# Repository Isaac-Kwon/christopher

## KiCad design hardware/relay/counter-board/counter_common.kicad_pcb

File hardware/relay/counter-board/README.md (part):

# 릴레이 계수기 보드 (Phase 3 R 트랙, 회로도)

작성일: 2026-11-15 · 상태: **회로도(KiCad 10) 생성·ERC·넷리스트 시뮬레이션 완료, 기판 배치(미배선) 생성·검증 완료, 결정 0003 8.4절(K1–K7) 반영(10절, K7 = 클럭 버스 B와 레일 버퍼는 11절), 배선은 사용자가** · 관련: `hardware/relay/concept.md` 5·6절, `docs/decisions/0001-test-register-timing.md`, `docs/decisions/0003-interfaces.md`, `hardware/relay/sequencer/README.md`(클럭 순서기, `CLK_A`/`CLK_B`), `hardware/common/design-brief.md`, `hardware/relay/shifter-board/README.md`, 기준 모델 `crates/christopher-core/src/relay.rs`(`Counters`, `Controls::from_cores`)

**표기.** **(계산)** = 이 문서의 산술, **(추정)** = 실측 전 값, **(미확인)** = 데이터시트로 확인하지 못한 것.

## 1. 무엇인가

`concept.md` 5.1절의 계수기 다섯 개(pL, pM, a3, a2, a1)와 a4 = l, 그리고 결정 0003이 더한 뱅크 수준의 r 자리(pR)를 릴레이와 다이오드(+ 저항, LED)만으로 만든다. 출력은 시프터 보드 J5의 `CTRL0..CTRL4`(24 V, 가중치 1, 2, 4, 8, 16)를 **그대로** 구동하는 5비트 이진값 0..25다. 모든 자리는 같은 회로(**릴레이 11개**)이고 보드는 두 장이다.

| 보드 | 내용 | 릴레이 | 다이오드 | 파일 |
|---|---|---:|---:|---|
| 공통 (`counter_common`) | pL(= a4 = l), pM, a3 = l − m, **pR(r, 프리셋 0)** 네 자리 + 자리 사이 규칙 배선 + **`POS` 커넥터 J4** + 전원 입력 J3 + **클럭 버스 B의 레일 버퍼**(pL·pM 주 릴레이의 쌍둥이 10개, `CLOCK_B` J5, `UNIT_BUS_B` J6; 11절) | 54 (44 + 10) | 279 | `counter_common.kicad_sch`, `common_pl/pm/a3/pr.kicad_sch` |
| 유닛별 (`counter_unit`) | a2, a1 두 자리(오프셋 다이얼 프리셋) + 공통 a3/a4 코드를 이 유닛의 시프터 보드 4장으로 중계하는 릴레이 10개 + 전원 입력 J7 | 32 (22 + 10) | 138 | `counter_unit.kicad_sch`, `unit_a2/a1/buf.kicad_sch` |

생성기 `gen_counter.py`(표준 라이브러리만, 시프터 보드와 같은 방식·심볼: `Relay:G6S-2`, D-sub, 라벨 연결), 검증기 `verify_counter.py`. 생성물은 UUID를 고정해 두었으므로 손으로 고치지 말고 생성기를 고친다.

## 2. 한 자리의 회로 (11 릴레이)

### 2.1 아이디어

비트마다 **슬레이브 릴레이 KS**(값을 갖고, 접점이 `CTRL`을 구동)와 **마스터 릴레이 KM**(항상 KS의 **반대값**을 따라가는 거울)을 둔다. 한 자리의 증가는 이진 올림 사슬에서 "토글해야 하는 비트"를 가려내고, 그 비트의 슬레이브가 마스터 값을 **한꺼번에** 받는 동작이다: 토글이므로 새 값 = 마스터 값 = 옛 값의 반대. 마스터가 클럭 동안 변하지 않으므로 올림 사슬은 접점만 지나가고 릴레이 동작을 기다리지 않는다(파문 올림이 아니라 순간 전달, 경주 없음).

신호는 모두 24 V "레일"(접점·다이오드를 거쳐 전달되는 +24 V)이고, 증가/정지는 상보 쌍으로 다룬다.

| 이름 | 뜻 |
|---|---|
| `AIN` / `ZIN` | 증가 레일 / 정지 레일 (항상 하나만 켜짐, 클럭 구간에서 `AIN` = 클럭 펄스 ∧ 이 자리의 증가 조건) |
| `AOUT` / `ZOUT` | 올림(25 → 0) 레일 쌍 = 다음 자리의 `AIN` / `ZIN` 재료 |
| `NOUT` | `AIN` ∧ (값 ≠ 25) |
| `P0..P4` | 프리셋 코드(다이얼). 24 V는 `LOAD` 동안에만 걸린다 |
| `Q0..Q4` | 값의 각 비트(1이면 24 V) = `CTRL` |

### 2.2 구성 (비트 i = 0..4)

- **KS_i** (극 1: COM = +24 V, NO → `Q_i`, NC → `NQ_i`; 극 2: COM = 레일 `Z_i`, NC → 마스터 거울, NO → 자기 유지).
- **KM_i** (극 1: COM = 사슬 `A_i`, NC → `A_{i+1}`(사슬 계속), NO → `G_i`(마스터 유지 + 슬레이브 적재 급전); 극 2: COM = `AIN`, NO → `Y_i` = `AIN` ∧ KM_i).
- **KW** (한 자리에 하나): 코일 = `NQ0 ∨ NQ4 ∨ NQ3`(다이오드 OR) = "값 ≠ 25". 접점 두 극이 비트 1, 2의 마스터 거울 경로에 직렬로 들어간다.
- 올림 사슬: `A_0 = AIN`, `A_{i+1} = A_i ∧ (마스터 i = 0)`(마스터 NC 접점) → 비트 i는 `A_i`가 올라올 때 토글. `A_5` = `AOUT`.
- 정지 레일: `Z_t = ZIN ∨ Y_0 ∨ … ∨ Y_{t−1}`(병렬 다이오드 OR, 한 노드에 다이오드 한 개 전압 강하) = `NOT A_t`.
- 슬레이브 코일 급전(다이오드로 OR): ① 자기 유지(레일 `Z_i` → KS 극 2 NO), ② 적재(`A_i` → KM NO = `G_i`, 마스터가 1일 때), ③ 프리셋(`P_i`). 마스터 코일 급전: ① 거울(레일 `Z_i` → KS 극 2 NC; 비트 1, 2는 KW 접점 경유), ② 유지(`G_i`).
- 코일마다 역기전력 다이오드(1N4148W), 급전·OR 다이오드는 쇼트키(1N5819W, 강하 약 0.3 V — 코일 전압 확보). 비트마다 `Q`에 저항 4.7 kΩ + LED(값 표시, 5 mA).

### 2.3 동작 (한 클럭)

클럭은 **두 상**이다. `NCK`(= 평상시 켜짐)와 `CK`(= 확정 펄스). 상보이며 겹치지 않는다(2.5절).

| 상 | 레일 | 마스터 | 슬레이브 |
|---|---|---|---|
| φ1 (`NCK`, 평상시) | 모든 `Z_i`가 켜짐, `A_i` 꺼짐 | 슬레이브의 반대값을 계속 따라감(**미리 계산**) | 자기 유지 |
| φ2 (`CK`, 확정) | `AIN`이 켜진 자리: 토글 비트의 `Z_i`가 꺼지고 `A_i`가 켜짐 | 토글 비트: 자기 유지(`G`)로 값을 붙잡음. 나머지: 계속 거울 | 토글 비트: 마스터 값을 받음. 나머지: 유지 |

- **정지**: `AIN` = 0이면 모든 `A_i` 꺼짐, 모든 슬레이브가 `Z_i`로 유지된다.
- **25 → 0**: 값이 25 = `11001b`일 때 KW가 꺼져 비트 1, 2의 거울이 끊기고(마스터는 `00000`), 이때만 마스터 전부가 0이 된다(정상 값에서 마스터 = NOT 값이 0이 되려면 값 = 31이어야 하므로 도달 불가). 마스터 NC가 모두 닫혀 있으므로 `A_0 … A_4`가 전부 올라와 슬레이브 다섯 개가 모두 0을 받는다. `A_5`가 올라와 **올림 = `AOUT` = `AIN` ∧ 값 = 25**가 된다. 따라서 25 → 0을 별도 감지·리셋 없이(과도 값 26 없이) 같은 사슬이 처리한다.
- 정상 증가에서 `A_{i+1} = A_i ∧ 슬레이브 i`이므로 이진 +1과 같다. 이진 코드 직접 구동이므로 시프터에 중간값이 안 보인다.
- `ZOUT = NOT AOUT`는 정지 레일이 상보를 유지하게 하는 쌍이다(`NCK`가 꺼진 φ2에서도 올림이 없으면 켜짐).

### 2.4 릴레이 수 (concept.md 추정과 비교)

한 자리: KS 5 + KM 5 + KW 1 = **11개**. `concept.md` 5.2절의 "비트당 2개 × 5 + 리셋·올림 2–3개 ≈ 13개"보다 2개 적다(올림은 마스터 접점 사슬이 하고, 26진 처리는 KW 하나다). 대신 다이오드가 한 자리 64개다(급전 25 + 정지 레일 OR 20 + `NOUT` OR 5 + KW 3 + 역기전력 11). 2연 다이오드 소자(SOT-23)를 쓰면 부품 수는 절반 근처로 준다 **(추정)**.

| 보드 | 자리 | 릴레이 | 비고 |
|---|---|---:|---|
| 공통 | pL, pM, a3 | 33 | `concept.md` 5.2절의 공통 계수 39 대비 −6 (클럭 발생·시작·정지·Home 제어 약 8은 별도 시퀀서) |
| 유닛 | a2, a1 | 22 | `concept.md`의 26 대비 −4 |
| 유닛 | a3/a4 중계 | 10 | 코일 = 공통 코드선, 접점 두 극 병렬 = 이 유닛의 `CTRL` 선 (`concept.md`의 "중계 릴레이 약 10") |
| 유닛 합계 | | **32** | `concept.md` 36 대비 −4 |
| 6유닛 합계 | | **225** (= 33 + 6 × 32) | `concept.md` 266 대비 |
| 12유닛 합계 | | **417** | `concept.md` 482 대비 |

이 비교에는 그 뒤에 더한 공통 보드의 pR(11개, 0003 K3)과 클럭 버스 B의 쌍둥이 주 릴레이(10개, 0003 K7, 11절)가 들어 있지 않다. 지금의 공통 보드는 54개, 12유닛 합계는 438개(= 54 + 12 × 32)다 **(계산)**.

(공통 클럭 발생·시퀀서는 이 보드에 없다.)

### 2.5 시퀀서에 요구하는 것

- `CK`/`NCK`는 **하나의 전환(c) 접점**에서 나온다(COM = +24 V, NO → `CK`, NC → `NCK`). 개별 릴레이 둘로 만들어 둘 다 켜지면 값이 틀어진다(시뮬레이션에서 확인: "info" 줄). 전환 중 양쪽이 모두 꺼지는 순간(break-before-make)은 릴레이 복귀 시간(3–5 ms, 결정 0001)보다 충분히 짧아야 한다(수 백 µs).
- **HOME(프리셋)**: ① `CK` = `NCK` = 0(전부 꺼짐)으로 모든 릴레이를 풀고, ② `LOAD` = 24 V로 다이얼 공통선에 전압을 걸어 슬레이브가 `P`를 받게 하고, ③ `NCK`를 올리되 **`LOAD`는 그 뒤에 내린다**(겹침 또는 틈 없이). `LOAD`가 `NCK`보다 먼저 내려가는 틈이 릴레이 복귀 시간보다 길면 프리셋이 지워진다(시뮬레이션: 틈 있는 순서는 실패).
- 전원 투입 직후의 릴레이 상태는 임의이며, 위 절차가 어떤 상태에서도 올바른 값을 만든다(무작위 초기 상태로 확인).

## 3. 계수 규칙의 배치 (`relay.rs` `Counters`)

| 계수기 | 증가 조건 | 구현 (`AIN` / `ZIN`) |
|---|---|---|
| pL (a4 = l) | 매 클럭 | `AIN = CK`, `ZIN = NCK` |
| pM | l이 25 → 0 | `AIN = LC` (= pL의 `AOUT`), `ZIN = ZL` (= pL의 `ZOUT`) |
| a3 = l − m | 매 클럭, 단 l이 25 → 0이면 정지 | `AIN = NL` (= pL의 `NOUT` = `CK ∧ l ≠ 25`), `ZIN = NCK ∨ LC` (다이오드 2개) |
| a2 | pM이 증가하고 m이 25 → 0이 아님 | `AIN = A2B` (= pM의 `NOUT` = `CK ∧ l 올림 ∧ m ≠ 25`, pM의 접점 극 2의 COM을 `LC`로 둔 덕분에 다이오드 없이 AND), `ZIN = Z2B = ZL ∨ A1B` (다이오드 2개) |
| a1 | m이 25 → 0 | `AIN = A1B` (= pM의 `AOUT`), `ZIN = Z1B` (= pM의 `ZOUT`) |

- **공통 보드**: 위 다섯 규칙 전부와 pM·a3 자리의 판정이 여기 있다. 유닛으로는 레일 4개(`A2B`, `Z2B`, `A1B`, `Z1B`)와 a4/a3 코드 10선(`L0..4`, `T0..4`)만 나간다.
- **유닛 보드**: 규칙 논리가 **없다**. a2/a1 자리는 공통 레일을 받아 증가/정지만 하고, 프리셋만 유닛별이다(다이얼: a1 = k, a2 = −k mod 26).
- pL·pM·a3의 `P0..P4`는 0 V에 묶어 **프리셋 = 0(clear)**. 오프셋과 무관하게 HOME에서 l = m = 0, a3 = 0이다.
- 모든 올림·판정이 **마스터 값**(φ2 동안 불변)에서 나오므로, 같은 클럭에서 슬레이브가 바뀌어도 규칙 신호가 흔들리지 않는다. 한 클럭의 모든 계수기가 같은 `CK` 펄스 안에서 동시에 움직이고, 사이의 순서(예: pM이 l보다 먼저/나중)가 없다.

## 4. 타이밍 (결정 0001과의 관계)

위치 한 칸(`concept.md` 6절)의 순서: **`CK` 펄스 → 슬레이브 전환 → (a3/a4는 중계 릴레이) → 시프터 전환·바운스 → `STROBE` → 감지 → `JUDGE` → `CLEAR` → `CK` 복귀 → 다음 `CK`**.

| 구간 | 대표 | 최대 | 비고 |
|---|---:|---:|---|
| 슬레이브 동작 (`CK` 상승부터) | 2.5 | 4 | a1, a2는 여기서 `CTRL` 확정 |
| a3/a4 중계 릴레이 | 2.5 | 4 | a3, a4만 해당(슬레이브 + 중계 = 5 / 8 ms). a1, a2는 중계 없이 슬레이브 접점이 시프터 코일을 구동 |
| `CK` 펄스 폭 | | ≥ 4 + 튐 1 = 5 | 슬레이브가 끝까지 움직일 때까지 `CK` 유지 **(계산)** |
| 마스터 재계산 (`CK` 하강부터) | 2.5 | 4 (복귀는 다이오드 포함 최대 10) | 슬레이브가 바뀐 뒤 KW와 마스터가 새 거울을 만든다. **`STROBE`·판정과 겹치는 구간**이므로 위치 시간에 더해지지 않는다 |

- 결정 0001의 표(대표 약 20 ms, 최대 약 33 ms)에서 계수기 항목(릴레이 2단, 대표 5 / 최대 8 ms)과 중계 릴레이(2.5 / 4 ms)는 이 설계에서 a3/a4 경로 = 슬레이브 + 중계(5 / 8 ms)와 a1/a2 경로 = 슬레이브 1단(2.5 / 4 ms)으로 줄어든다. 마스터는 "미리 계산"으로 클럭 경로 밖에 있으므로 클럭 경로에는 **슬레이브 1단**만 있다. 그러므로 표의 두 항목 합(7.5 / 12 ms)이 최악 경로 5 / 8 ms로 줄어 합계는 대표 약 17.5 / 최대 약 29 ms **(계산)**.
- 마스터가 다음 `CK` 전에 정착해야 한다: 슬레이브(4) → KW(4) → 마스터(복귀 최대 10) ≈ 18 ms 최대 **(계산)**. `CK` 하강부터 다음 상승까지 25 ms 목표에서 `CK` 폭 5 ms를 빼면 20 ms가 남아 맞는다. 33 ms 예비안에서도 성립. 이 여유는 R.1에서 실측(항목 2).
- `JUDGE`·`CLEAR`는 테스트 레지스터 쪽 신호이며 계수기와 신호를 주고받지 않는다. 다음 `CK`는 `CLEAR` 뒤에만 나가도록 클럭 시퀀서가 정한다(계수기 보드는 이를 모른다).
- 관찰 모드(≤ 4 위치/초)와 한 스텝 버튼: `CK`를 한 번 누르는 것이 한 클럭이다. 마스터가 자동으로 다음 값을 준비해 두므로 버튼 사이 간격에 제약이 없다.

## 5. 커넥터

모두 D-sub 수(핀) 직각 PCB 장착, 케이블은 암–암(시프터 보드 규약과 같음).

| 보드 | 참조 | 이름 | 핀 |
|---|---|---|---|
| 공통 | J1 | CLOCK (DE9) | **클럭 버스 A**(순서기 J3 `CLK_A`): 1 `CK`, 2 `NCK`, 3 `LOAD`, **4–5 예약(전에는 +24 V)**, 6–7 0 V, 8–9 예약 |
| 공통 | J2 | UNIT_BUS (DB25) | **유닛 1–6**: 1 `A2B`, 2 `Z2B`, 3 `A1B`, 4 `Z1B`, 5–9 `L0..L4`(a4 = l 코드), 10–14 `T0..T4`(a3 코드), 15 `LOAD`, **16–18 예약(전에는 +24 V)**, 19–21 0 V, 22–25 예약 |
| 공통 | J5 | CLOCK_B (DE9) | **클럭 버스 B**(순서기 J4 `CLK_B`), J1과 같은 배치: 1 `CK_B`, 2 `NCK_B`, 3 `LOAD_B`, 4–5·8–9 예약, 6–7 0 V. 11절 |
| 공통 | J6 | UNIT_BUS_B (DB25) | **유닛 7–12**, J2와 같은 배치: 1 `A2B_B`, 2 `Z2B_B`, 3 `A1B_B`, 4 `Z1B_B`(버스 B의 레일, J5에서만 먹음), 5–14 `L0..L4`·`T0..T4`(J2와 같은 넷), 15 `LOAD_B`, 16–18·22–25 예약, 19–21 0 V. 유닛 보드는 같은 것이고 어느 리본에 꽂히는지만 다르다. 11절 |
| 공통 | J3 | 24V_IN (5.08 mm 2극 단자) | 1 = +24 V, 2 = 0 V. 보드의 +24 V는 여기서만 받는다(PTC 1 A → 직렬 P채널 MOSFET → TVS 33 V + 100 µF) |
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
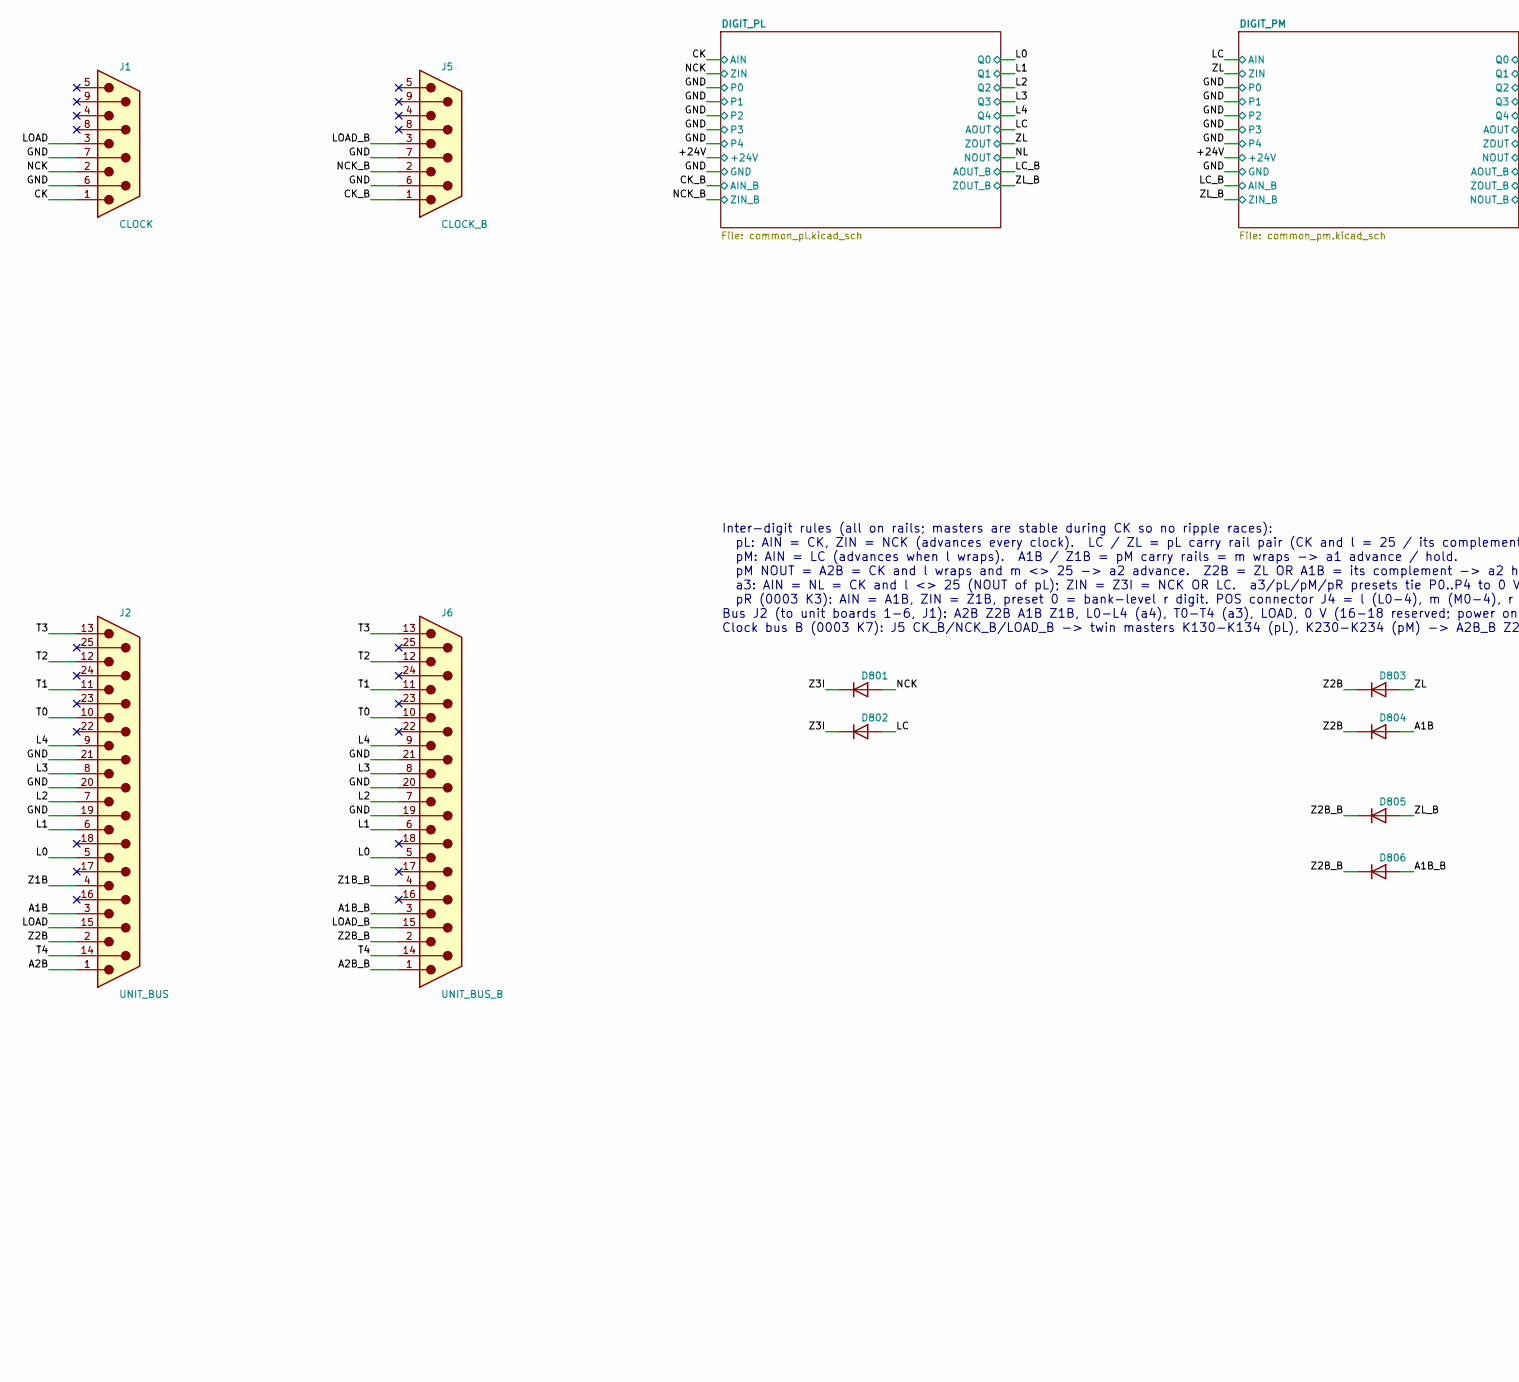
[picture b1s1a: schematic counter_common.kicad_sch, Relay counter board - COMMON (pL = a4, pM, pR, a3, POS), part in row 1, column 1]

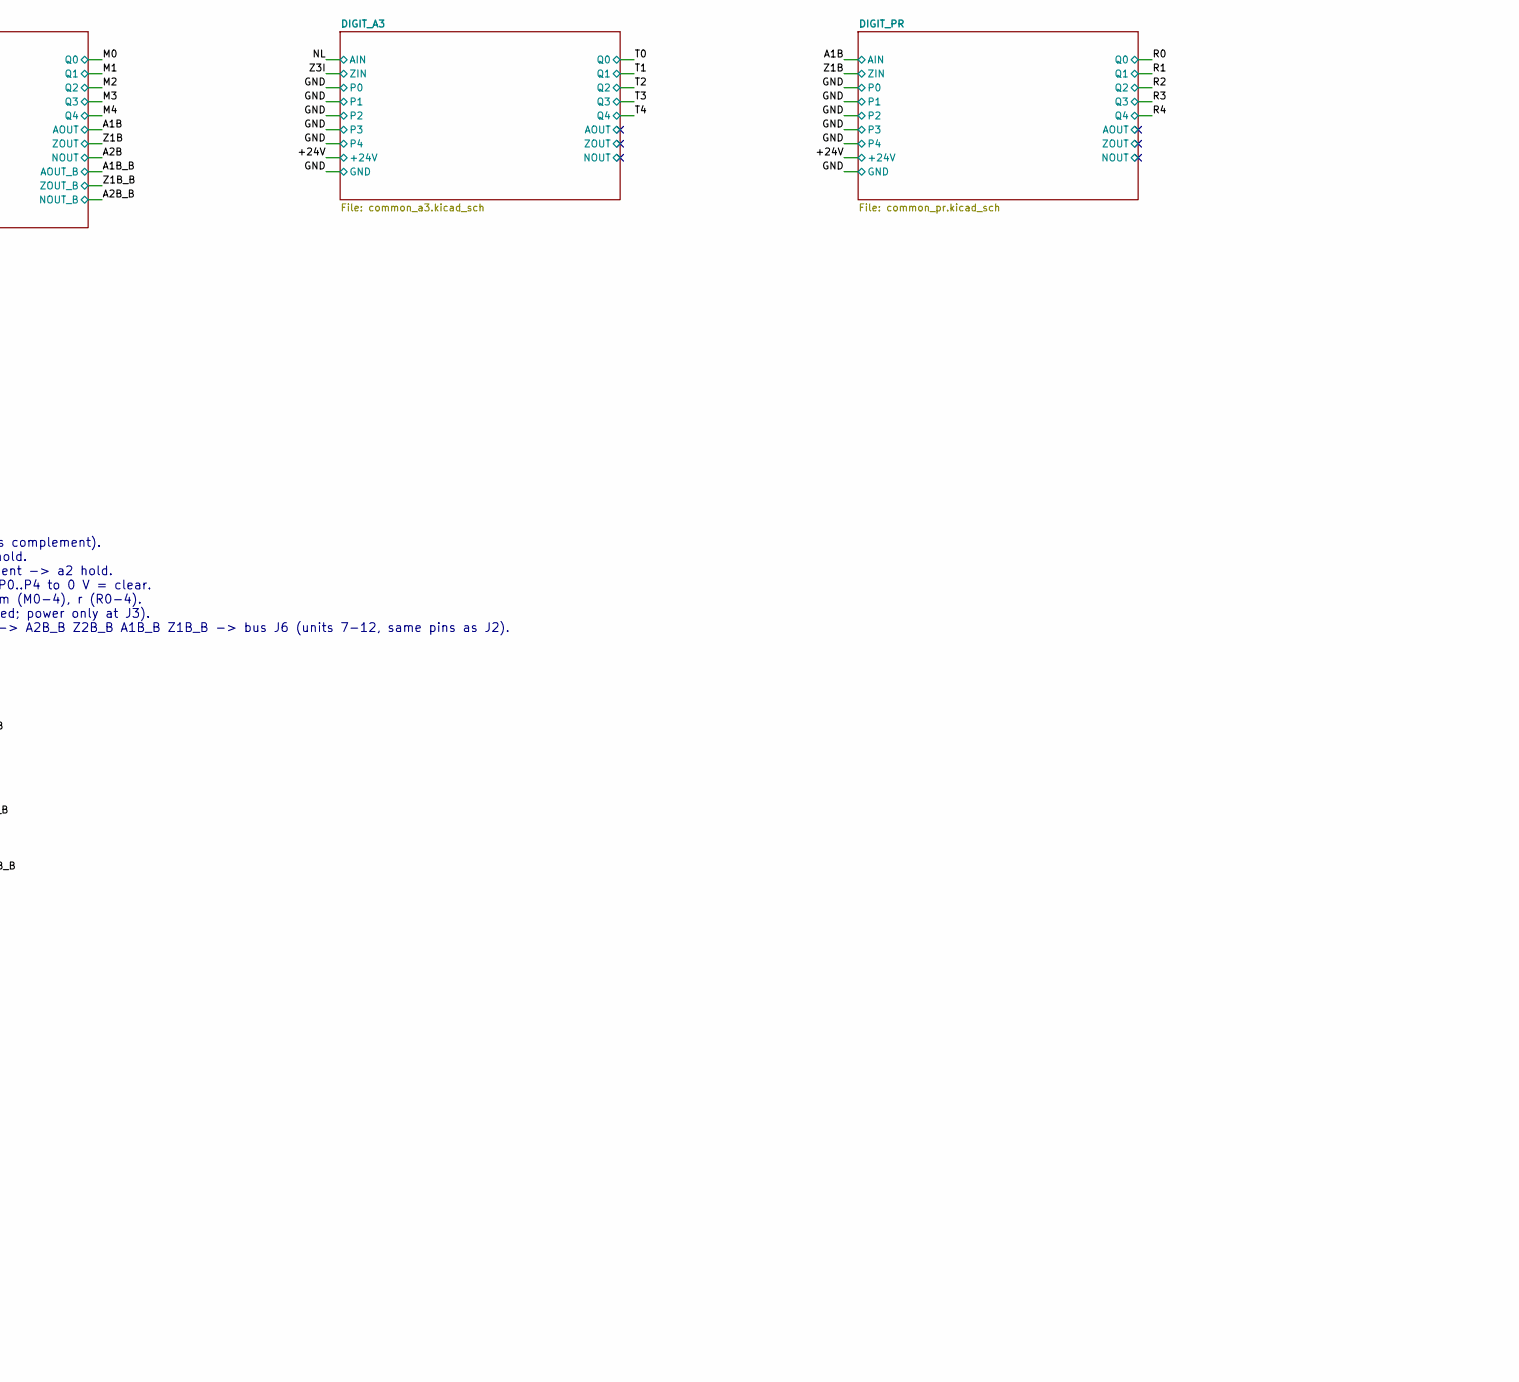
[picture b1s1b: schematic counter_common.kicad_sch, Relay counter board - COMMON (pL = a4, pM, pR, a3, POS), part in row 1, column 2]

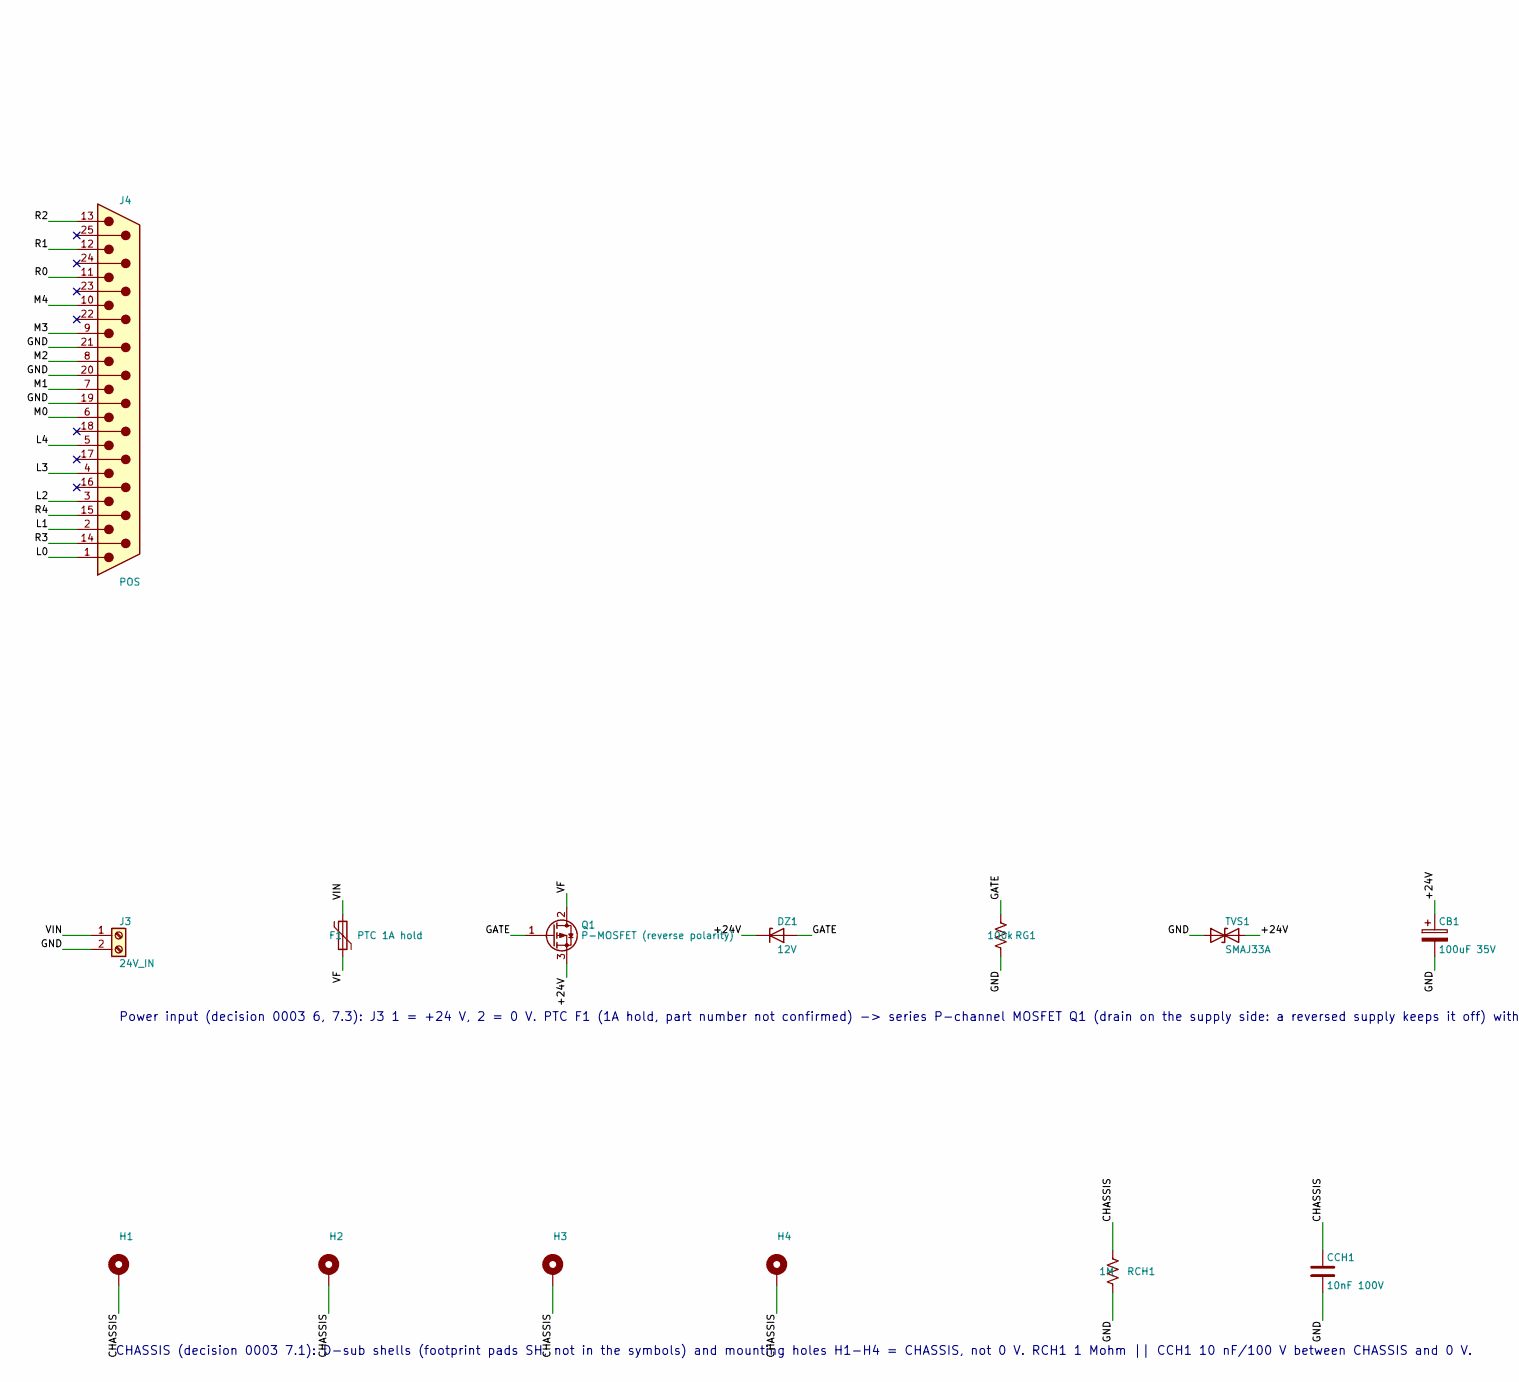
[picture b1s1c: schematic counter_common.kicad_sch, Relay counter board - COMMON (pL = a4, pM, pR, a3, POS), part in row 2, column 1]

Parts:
CB1: 100uF 35V; CP_Radial_D8.0mm_P3.50mm
CCH1: 10nF 100V; C_0603_1608Metric
D801, D802, D803, D804, D805, D806: 1N5819W; D_SOD-123
DZ1: 12V; D_SOD-123
F1: PTC 1A hold; Fuse_1812_4532Metric
H1, H2, H3, H4: MountingHole_Pad; MountingHole_3.2mm_M3_Pad
J1: CLOCK; DSUB-9_Pins_Horizontal_P2.77x2.84mm_EdgePinOffset9.90mm_Hou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
J2: UNIT_BUS; DSUB-25_Pins_Horizontal_P2.77x2.84mm_EdgePinOffset9.90mm_Ho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
J3: 24V_IN; TerminalBlock_Phoenix_MKDS-1,5-2-5.08_1x02_P5.08mm_Horizont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
J4: POS; DSUB-25_Pins_Horizontal_P2.77x2.84mm_EdgePinOffset9.90mm_Ho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
J5: CLOCK_B; DSUB-9_Pins_Horizontal_P2.77x2.84mm_EdgePinOffset9.90mm_Hou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
J6: UNIT_BUS_B; DSUB-25_Pins_Horizontal_P2.77x2.84mm_EdgePinOffset9.90mm_Ho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
Q1: P-MOSFET (reverse polarity); SOT-223-3_TabPin2
RCH1: 1M; R_0603_1608Metric
RG1: 100k; R_0603_1608Metric
TVS1: SMAJ33A; D_SMA

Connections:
/+24V: CB1.1, DZ1.1 (K), Q1.3 (S), TVS1.2 (A2); also elsewhere on the board
/A1B: D804.2 (A), J2.3; also elsewhere on the board
/A1B_B: D806.2 (A), J6.3; also elsewhere on the board
/A2B: J2.1; also elsewhere on the board
/A2B_B: J6.1; also elsewhere on the board
/CHASSIS: CCH1.1, H1.1, H2.1, H3.1, H4.1, J1.SH, J2.SH, J4.SH, J5.SH, J6.SH, RCH1.1
/CK: J1.1; also elsewhere on the board
/CK_B: J5.1; also elsewhere on the board
/GATE: DZ1.2 (A), Q1.1 (G), RG1.1
/GND: CB1.2, CCH1.2, J1.6, J1.7, J2.19, J2.20, J2.21, J3.2, J4.19, J4.20, J4.21, J5.6, J5.7, J6.19, J6.20, J6.21, RCH1.2, RG1.2, TVS1.1 (A1); also elsewhere on the board
/L0: J2.5, J4.1, J6.5; also elsewhere on the board
/L1: J2.6, J4.2, J6.6; also elsewhere on the board
/L2: J2.7, J4.3, J6.7; also elsewhere on the board
/L3: J2.8, J4.4, J6.8; also elsewhere on the board
/L4: J2.9, J4.5, J6.9; also elsewhere on the board
/LC: D802.2 (A); also elsewhere on the board
/LOAD: J1.3, J2.15
/LOAD_B: J5.3, J6.15
/M0: J4.6; also elsewhere on the board
/M1: J4.7; also elsewhere on the board
/M2: J4.8; also elsewhere on the board
/M3: J4.9; also elsewhere on the board
/M4: J4.10; also elsewhere on the board
/NCK: D801.2 (A), J1.2; also elsewhere on the board
/NCK_B: J5.2; also elsewhere on the board
/R0: J4.11; also elsewhere on the board
/R1: J4.12; also elsewhere on the board
/R2: J4.13; also elsewhere on the board
/R3: J4.14; also elsewhere on the board
/R4: J4.15; also elsewhere on the board
/T0: J2.10, J6.10; also elsewhere on the board
/T1: J2.11, J6.11; also elsewhere on the board
/T2: J2.12, J6.12; also elsewhere on the board
/T3: J2.13, J6.13; also elsewhere on the board
/T4: J2.14, J6.14; also elsewhere on the board
/VF: F1.2, Q1.2 (D)
/VIN: F1.1, J3.1
/Z1B: J2.4; also elsewhere on the board
/Z1B_B: J6.4; also elsewhere on the board
/Z2B: D803.1 (K), D804.1 (K), J2.2
/Z2B_B: D805.1 (K), D806.1 (K), J6.2
/Z3I: D801.1 (K), D802.1 (K); also elsewhere on the board
/ZL: D803.2 (A); also elsewhere on the board
/ZL_B: D805.2 (A); also elsewhere on the board

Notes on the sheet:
Power input (decision 0003 6, 7.3): J3 1 = +24 V, 2 = 0 V. PTC F1 (1A hold, part number not confirmed) -> series P-channel MOSFET Q1 (drain on the supply side: a reversed supply keeps it off) with gate zener DZ1 12 V + RG1 -> TVS1 33 V and CB1 100 uF/35 V. The board +24V is taken only from here; no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
CHASSIS (decision 0003 7.1): D-sub shells (footprint pads SH, not in the symbols) and mounting holes H1-H4 = CHASSIS, not 0 V. RCH1 1 Mohm || CCH1 10 nF/100 V between CHASSIS and 0 V.
Inter-digit rules (all on rails; masters are stable during CK so no ripple races): pL: AIN = CK, ZIN = NCK (advances every clock). LC / ZL = pL carry rail pair (CK and l = 25 / its complement). pM: AIN = LC (advances when l wraps). A1B / Z1B = pM carry rails = m wraps -> a1 advance / hold. pM NOUT 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

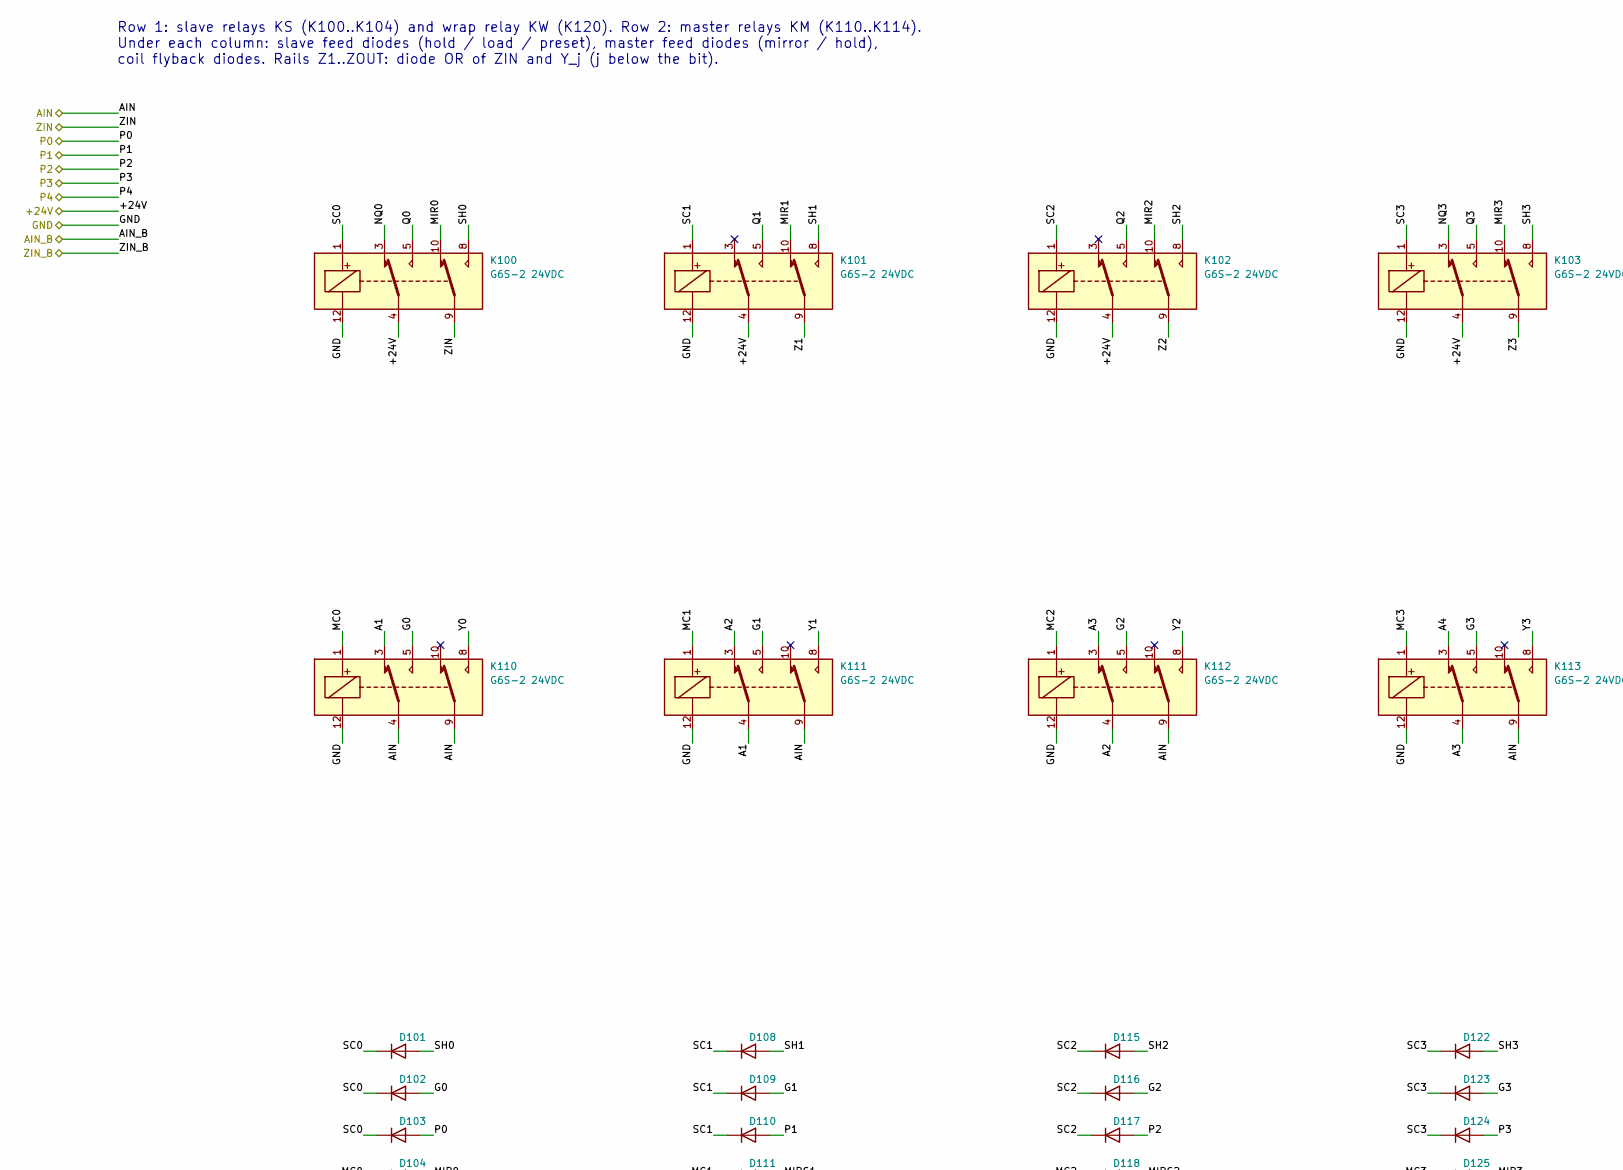
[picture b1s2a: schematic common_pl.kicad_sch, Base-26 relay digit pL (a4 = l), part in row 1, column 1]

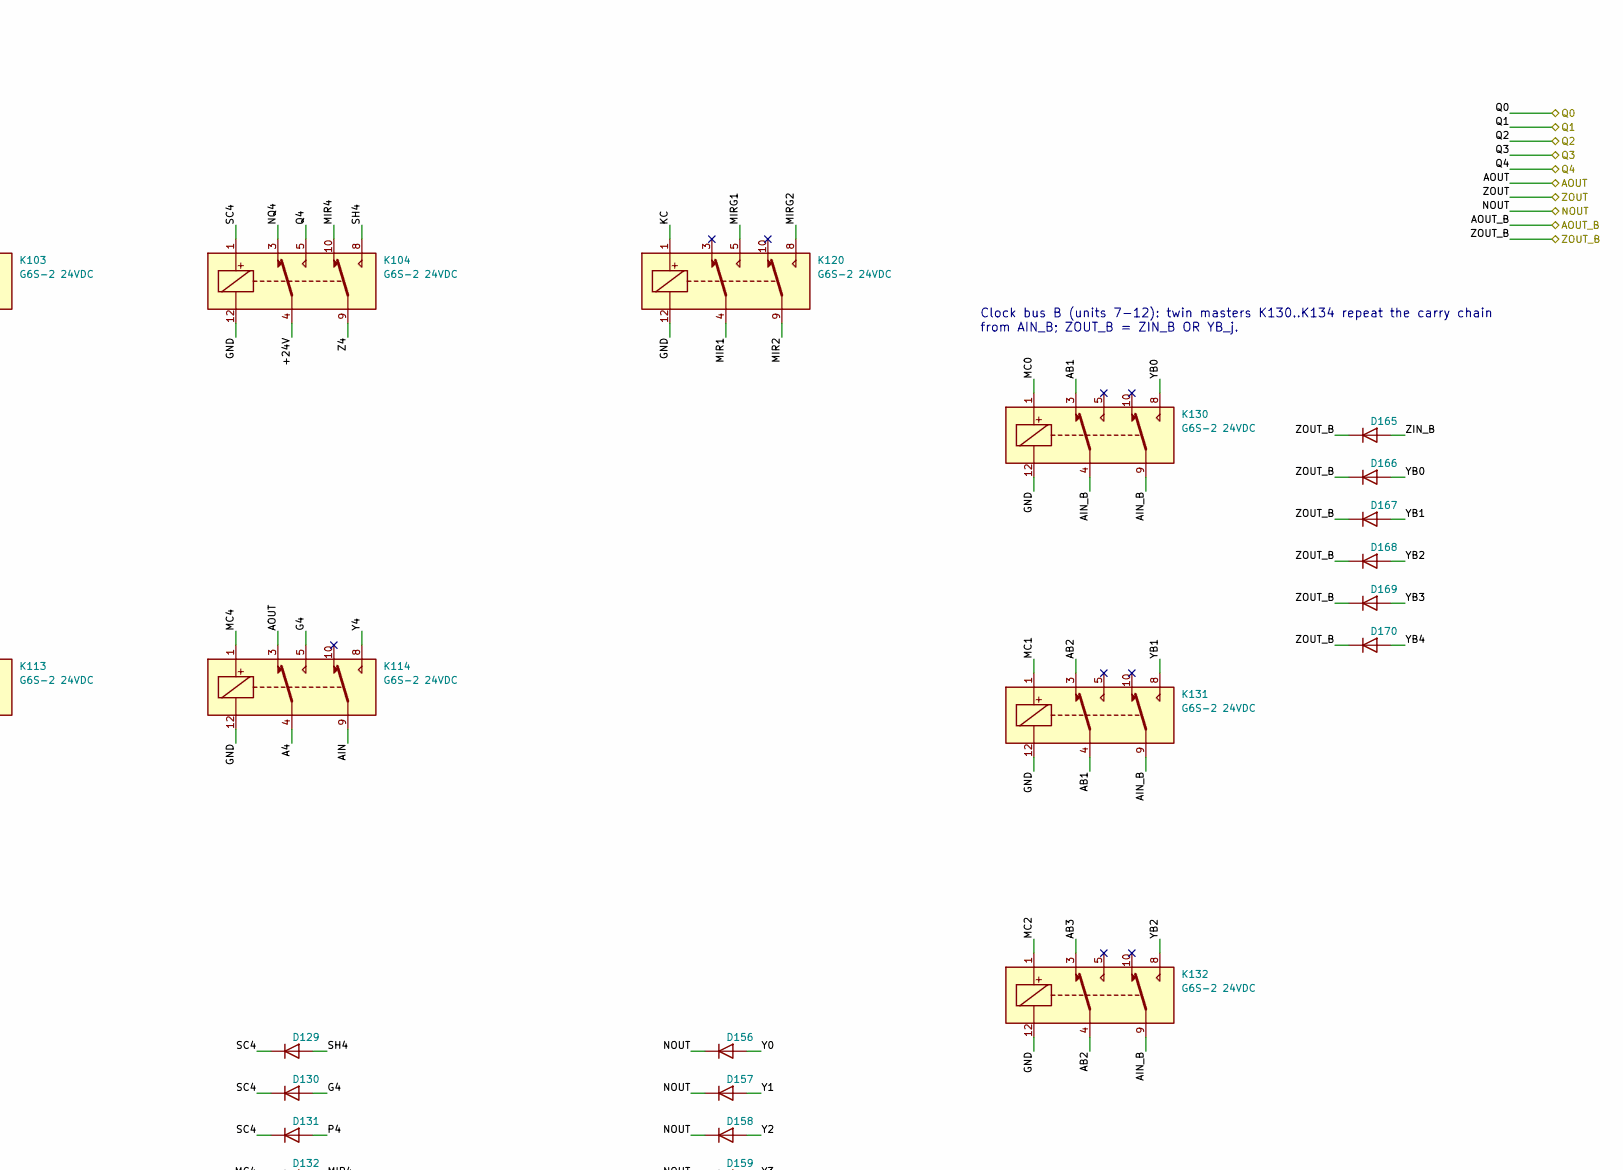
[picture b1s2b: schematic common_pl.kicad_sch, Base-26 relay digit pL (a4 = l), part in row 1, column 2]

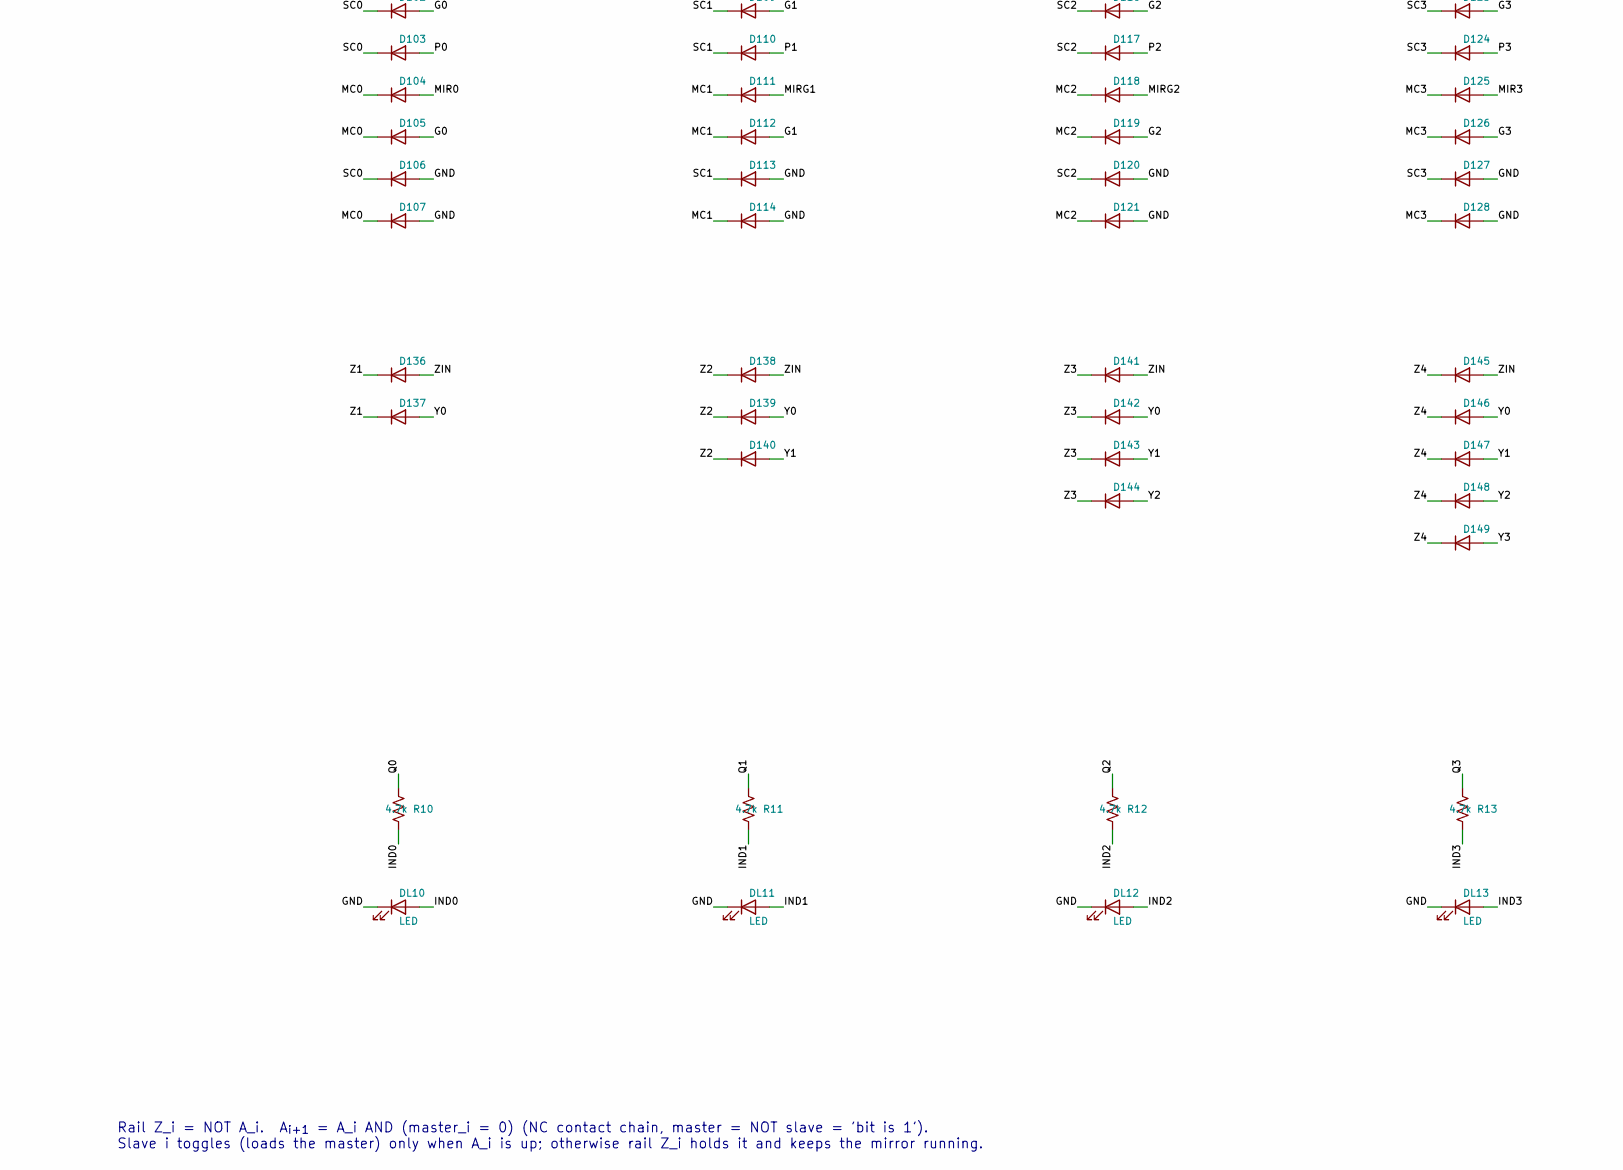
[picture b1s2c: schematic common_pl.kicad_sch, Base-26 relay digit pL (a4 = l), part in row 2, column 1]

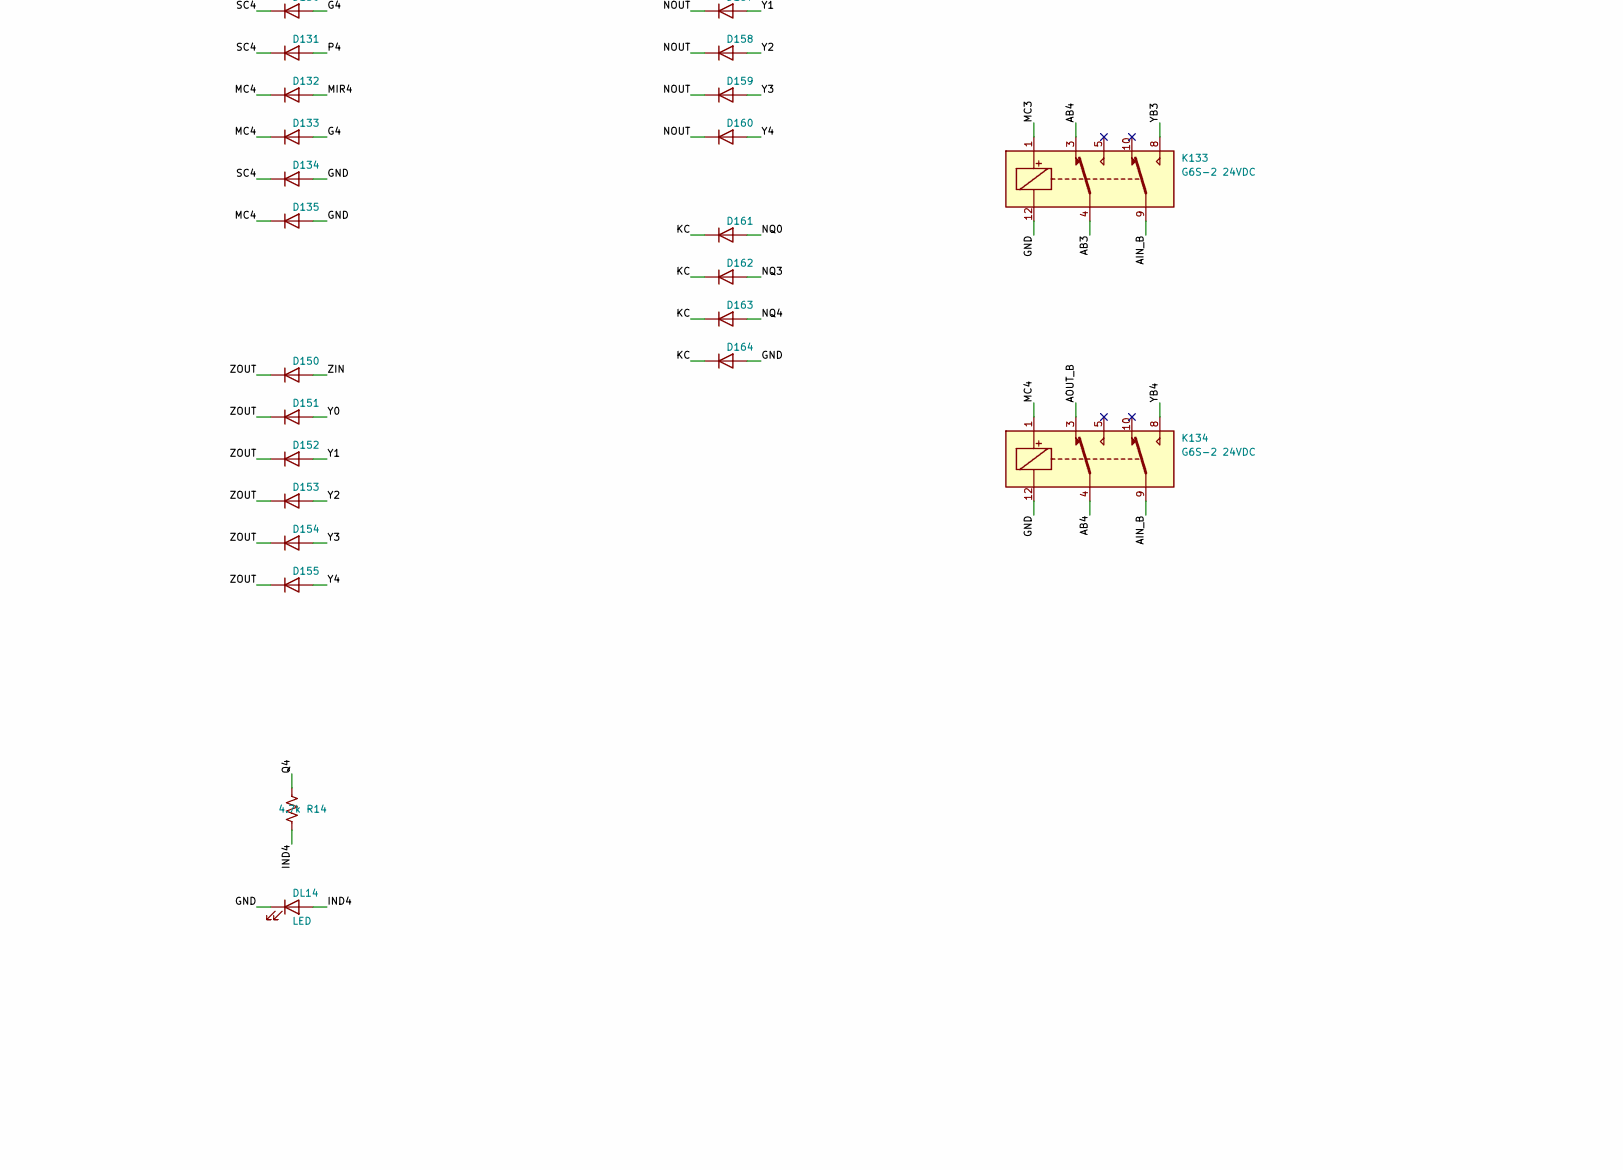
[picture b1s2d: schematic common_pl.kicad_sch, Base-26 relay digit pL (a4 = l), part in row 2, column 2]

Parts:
D101, D102, D103, D104, D105, D108, D109, D110, D111, D112, D115, D116, D117, D118, D119, D122, D123, D124, D125, D126, D129, D130, D131, D132, D133, D136, D137, D138, D139, D140, D141, D142, D143, D144, D145, D146, D147, D148, D149, D150, D151, D152, D153, D154, D155, D156, D157, D158, D159, D160, D161, D162, D163, D165, D166, D167, D168, D169, D170: 1N5819W; D_SOD-123
D106, D107, D113, D114, D120, D121, D127, D128, D134, D135, D164: 1N4148W; D_SOD-123
DL10, DL11, DL12, DL13, DL14: LED; LED_0603_1608Metric
K100, K101, K102, K103, K104, K110, K111, K112, K113, K114, K120, K130, K131, K132, K133, K134: G6S-2 24VDC; Relay_DPDT_Omron_G6S-2
R10, R11, R12, R13, R14: 4.7k; R_0603_1608Metric

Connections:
/+24V: K100.4, K101.4, K102.4, K103.4, K104.4; also elsewhere on the board
/CK: K110.4, K110.9, K111.9, K112.9, K113.9, K114.9; also elsewhere on the board
/CK_B: K130.4, K130.9, K131.9, K132.9, K133.9, K134.9; also elsewhere on the board
/DIGIT_PL/A1: K110.3, K111.4
/DIGIT_PL/A2: K111.3, K112.4
/DIGIT_PL/A3: K112.3, K113.4
/DIGIT_PL/A4: K113.3, K114.4
/DIGIT_PL/AB1: K130.3, K131.4
/DIGIT_PL/AB2: K131.3, K132.4
/DIGIT_PL/AB3: K132.3, K133.4
/DIGIT_PL/AB4: K133.3, K134.4
/DIGIT_PL/G0: D102.2 (A), D105.2 (A), K110.5
/DIGIT_PL/G1: D109.2 (A), D112.2 (A), K111.5
/DIGIT_PL/G2: D116.2 (A), D119.2 (A), K112.5
/DIGIT_PL/G3: D123.2 (A), D126.2 (A), K113.5
/DIGIT_PL/G4: D130.2 (A), D133.2 (A), K114.5
/DIGIT_PL/IND0: DL10.2 (A), R10.2
/DIGIT_PL/IND1: DL11.2 (A), R11.2
/DIGIT_PL/IND2: DL12.2 (A), R12.2
/DIGIT_PL/IND3: DL13.2 (A), R13.2
/DIGIT_PL/IND4: DL14.2 (A), R14.2
/DIGIT_PL/KC: D161.1 (K), D162.1 (K), D163.1 (K), D164.1 (K), K120.1
/DIGIT_PL/MC0: D104.1 (K), D105.1 (K), D107.1 (K), K110.1, K130.1
/DIGIT_PL/MC1: D111.1 (K), D112.1 (K), D114.1 (K), K111.1, K131.1
/DIGIT_PL/MC2: D118.1 (K), D119.1 (K), D121.1 (K), K112.1, K132.1
/DIGIT_PL/MC3: D125.1 (K), D126.1 (K), D128.1 (K), K113.1, K133.1
/DIGIT_PL/MC4: D132.1 (K), D133.1 (K), D135.1 (K), K114.1, K134.1
/DIGIT_PL/MIR0: D104.2 (A), K100.10
/DIGIT_PL/MIR1: K101.10, K120.4
/DIGIT_PL/MIR2: K102.10, K120.9
/DIGIT_PL/MIR3: D125.2 (A), K103.10
/DIGIT_PL/MIR4: D132.2 (A), K104.10
/DIGIT_PL/MIRG1: D111.2 (A), K120.5
/DIGIT_PL/MIRG2: D118.2 (A), K120.8
/DIGIT_PL/NQ0: D161.2 (A), K100.3
/DIGIT_PL/NQ3: D162.2 (A), K103.3
/DIGIT_PL/NQ4: D163.2 (A), K104.3
/DIGIT_PL/SC0: D101.1 (K), D102.1 (K), D103.1 (K), D106.1 (K), K100.1
/DIGIT_PL/SC1: D108.1 (K), D109.1 (K), D110.1 (K), D113.1 (K), K101.1
/DIGIT_PL/SC2: D115.1 (K), D116.1 (K), D117.1 (K), D120.1 (K), K102.1
/DIGIT_PL/SC3: D122.1 (K), D123.1 (K), D124.1 (K), D127.1 (K), K103.1
/DIGIT_PL/SC4: D129.1 (K), D130.1 (K), D131.1 (K), D134.1 (K), K104.1
/DIGIT_PL/SH0: D101.2 (A), K100.8
/DIGIT_PL/SH1: D108.2 (A), K101.8
/DIGIT_PL/SH2: D115.2 (A), K102.8
/DIGIT_PL/SH3: D122.2 (A), K103.8
/DIGIT_PL/SH4: D129.2 (A), K104.8
/DIGIT_PL/Y0: D137.2 (A), D139.2 (A), D142.2 (A), D146.2 (A), D151.2 (A), D156.2 (A), K110.8
/DIGIT_PL/Y1: D140.2 (A), D143.2 (A), D147.2 (A), D152.2 (A), D157.2 (A), K111.8
/DIGIT_PL/Y2: D144.2 (A), D148.2 (A), D153.2 (A), D158.2 (A), K112.8
/DIGIT_PL/Y3: D149.2 (A), D154.2 (A), D159.2 (A), K113.8
/DIGIT_PL/Y4: D155.2 (A), D160.2 (A), K114.8
/DIGIT_PL/YB0: D166.2 (A), K130.8
/DIGIT_PL/YB1: D167.2 (A), K131.8
/DIGIT_PL/YB2: D168.2 (A), K132.8
/DIGIT_PL/YB3: D169.2 (A), K133.8
/DIGIT_PL/YB4: D170.2 (A), K134.8
/DIGIT_PL/Z1: D136.1 (K), D137.1 (K), K101.9
/DIGIT_PL/Z2: D138.1 (K), D139.1 (K), D140.1 (K), K102.9
/DIGIT_PL/Z3: D141.1 (K), D142.1 (K), D143.1 (K), D144.1 (K), K103.9
/DIGIT_PL/Z4: D145.1 (K), D146.1 (K), D147.1 (K), D148.1 (K), D149.1 (K), K104.9
/GND: D103.2 (A), D106.2 (A), D107.2 (A), D110.2 (A), D113.2 (A), D114.2 (A), D117.2 (A), D120.2 (A), D121.2 (A), D124.2 (A), D127.2 (A), D128.2 (A), D131.2 (A), D134.2 (A), D135.2 (A), D164.2 (A), DL10.1 (K), DL11.1 (K), DL12.1 (K), DL13.1 (K), DL14.1 (K), K100.12, K101.12, K102.12, K103.12, K104.12, K110.12, K111.12, K112.12, K113.12, K114.12, K120.12, K130.12, K131.12, K132.12, K133.12, K134.12; also elsewhere on the board
/L0: K100.5, R10.1; also elsewhere on the board
/L1: K101.5, R11.1; also elsewhere on the board
/L2: K102.5, R12.1; also elsewhere on the board
/L3: K103.5, R13.1; also elsewhere on the board
/L4: K104.5, R14.1; also elsewhere on the board
/LC: K114.3; also elsewhere on the board
/LC_B: K134.3; also elsewhere on the board
/NCK: D136.2 (A), D138.2 (A), D141.2 (A), D145.2 (A), D150.2 (A), K100.9; also elsewhere on the board
/NCK_B: D165.2 (A); also elsewhere on the board
/NL: D156.1 (K), D157.1 (K), D158.1 (K), D159.1 (K), D160.1 (K); also elsewhere on the board
/ZL: D150.1 (K), D151.1 (K), D152.1 (K), D153.1 (K), D154.1 (K), D155.1 (K); also elsewhere on the board
/ZL_B: D165.1 (K), D166.1 (K), D167.1 (K), D168.1 (K), D169.1 (K), D170.1 (K); also elsewhere on the board

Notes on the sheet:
Clock bus B (units 7-12): twin masters K130..K134 repeat the carry chain from AIN_B; ZOUT_B = ZIN_B OR YB_j.
Row 1: slave relays KS (K100..K104) and wrap relay KW (K120). Row 2: master relays KM (K110..K114). Under each column: slave feed diodes (hold / load / preset), master feed diodes (mirror / hold), coil flyback diodes. Rails Z1..ZOUT: diode OR of ZIN and Y_j (j below the bit).
Rail Z_i = NOT A_i. A_{i+1} = A_i AND (master_i = 0) (NC contact chain, master = NOT slave = 'bit is 1'). Slave i toggles (loads the master) only when A_i is up; otherwise rail Z_i holds it and keeps the mirror running.
